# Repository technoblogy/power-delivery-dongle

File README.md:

# Power Delivery Dongle
A small board that will deliver one of six fixed voltages from a USB-C power adapter that supports Power Delivery.

For more information see <http://www.technoblogy.com/show?5729>.

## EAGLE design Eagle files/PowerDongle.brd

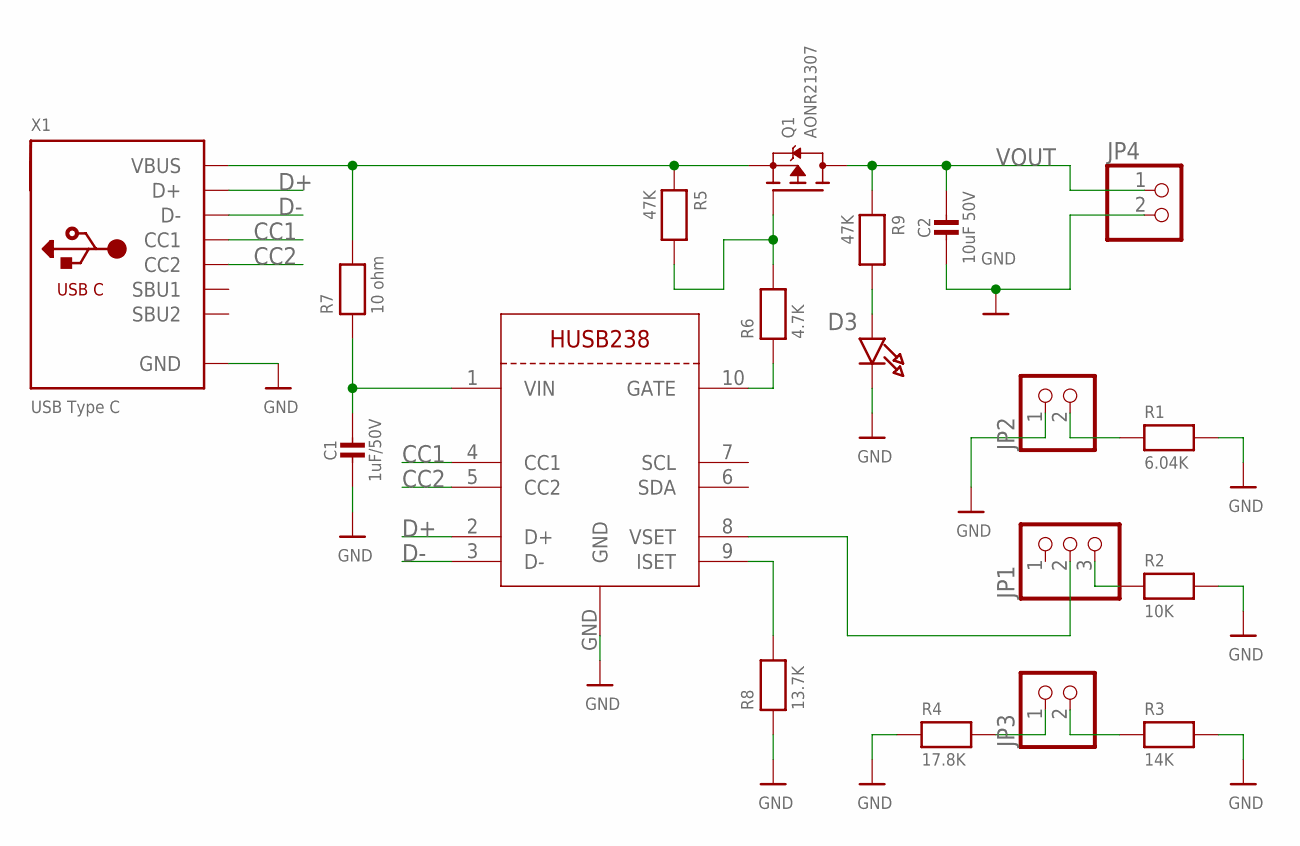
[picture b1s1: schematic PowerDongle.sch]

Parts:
C1: 1uF/50V; _0805MP
C2: 10uF 50V; _0805MP
D3: Green; CHIPLED_0805_NOOUTLINE
JP1: HEADER-1X3ROUND; 1X03_ROUND
JP2, JP3, JP4: HEADER-1X2ROUND; 1X02_ROUND
Q1: AONR21307; POWERDI3333
R1: 6.04K; _0805MP
R2: 10K; _0805MP
R3: 14K; _0805MP
R4: 17.8K; _0805MP
R5, R9: 47K; _0805MP
R6: 4.7K; _0805MP
R7: 10 ohm; _0805MP
R8: 13.7K; _0805MP
X1: USB Type C; USB_C_CUSB31-CFM2AX-01-X
X3: HUSB238; DFN10_3X3MM

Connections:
CC1: X1.A5 (CC1), X3.4 (CC1)
CC2: X1.B5 (CC2), X3.5 (CC2)
D+: X1.A6 (D+), X1.B6 (D+), X3.2 (D+)
D-: X1.A7 (D-), X1.B7 (D-), X3.3 (D-)
GND: C1.2, C2.2, D3.C, JP2.1, JP4.2, R1.2, R2.2, R3.2, R4.1, R8.1, X1.A1B12 (GND), X1.B1A12 (GND), X3.GND
unnamed: C1.1, R7.1, X3.1 (VIN)
unnamed: Q1.4 (G), R5.2, R6.2
unnamed: D3.A, R9.2
unnamed: R6.1, X3.10 (GATE)
unnamed: R8.2, X3.9 (ISET)
unnamed: JP2.2, R1.1
unnamed: JP1.3, R2.1
unnamed: JP1.2, X3.8 (VSET)
unnamed: JP3.2, R3.1
unnamed: JP3.1, R4.2
VBUS: Q1.1 (S), Q1.2 (S), Q1.3 (S), R5.1, R7.2, X1.A4B9 (VBUS), X1.B4A9 (VBUS)
VOUT: C2.1, JP4.1, Q1.5678 (D), R9.1

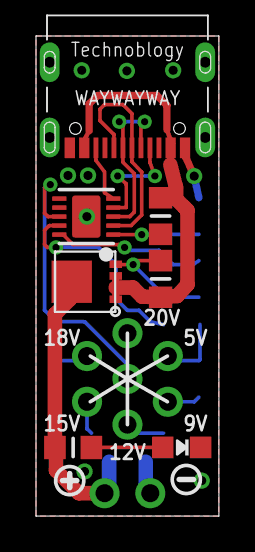
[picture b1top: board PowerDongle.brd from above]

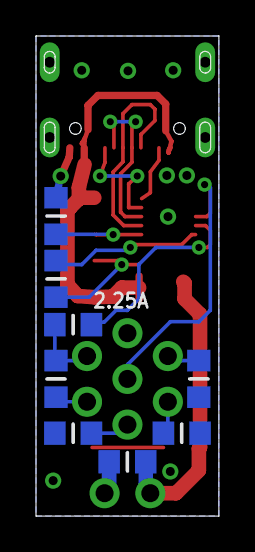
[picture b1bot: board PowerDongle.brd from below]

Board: 2 copper layers, 10.2 x 26.7 mm, 21 parts (8 on the bottom side), 17 nets.

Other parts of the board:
U$7: SYMBOL_PLUS
U$14: SYMBOL_MINUS

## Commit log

2025-11-18 Version 1 - 18th November 2025
2026-02-28 CC BY-SA 4.0

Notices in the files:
parts and their libraries:
microbuilder: This work is placed in the public domain, and may be freely used for commercial and non-commercial work with the following conditions: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
